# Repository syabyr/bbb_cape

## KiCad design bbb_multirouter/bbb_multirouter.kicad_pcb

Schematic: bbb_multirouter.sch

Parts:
J1: Conn_01x06; PinSocket_1x06_P2.54mm_Vertical
J2: Conn_01x02; PinSocket_1x02_P2.54mm_Vertical
J3: USB_C_Receptacle; USB_C_Receptacle_HRO_TYPE-C-31-M-12
P8, P9: BeagleBone_Black_Header; Socket_BeagleBone_Black
SW1, SW2, SW3: SW_Push; turtlekey

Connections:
+3V3: P9.3, P9.4; also elsewhere on the board
+5V: J3.A4 (VBUS), J3.A9 (VBUS), J3.B4 (VBUS), J3.B9 (VBUS), P9.5, P9.6
AIN0: P9.39
AIN1: P9.40
AIN2: P9.37
AIN3: P9.38
AIN4: P9.33
AIN5: P9.36
AIN6: P9.35
ECAPPWM0: P9.42
EHRPWM1A: P9.14
EHRPWM1B: P9.16
EHRPWM2A: P8.19
EHRPWM2B: P8.13
GND: J1.1, J3.A1 (GND), J3.A12 (GND), J3.B1 (GND), J3.B12 (GND), J3.S1 (SHIELD), P8.1, P8.2, P9.1, P9.2, P9.43, P9.44, P9.45, P9.46, SW1.2, SW2.2, SW3.2; also elsewhere on the board
GNDA_ADC: P9.34
GPIO_20: P9.41
GPIO_26: P8.14
GPIO_27: P8.17
GPIO_44: P8.12
GPIO_45: P8.11
GPIO_46: P8.16
GPIO_47: P8.15
GPIO_48: P9.15
GPIO_49: P9.23
GPIO_60: P9.12
GPIO_61: P8.26
GPIO_65: P8.18
GPIO_66: P8.7
GPIO_67: P8.8
GPIO_68: P8.10
GPIO_69: P8.9
GPIO_112: P9.30
GPIO_115: P9.27
GPIO_117: P9.25
I2C2_SCL: P9.19
I2C2_SDA: P9.20
LCD_AC_BIAS: P8.30
LCD_DATA0: P8.45; also elsewhere on the board
LCD_DATA1: P8.46; also elsewhere on the board
LCD_DATA2: P8.43, SW3.1
LCD_DATA3: P8.44
LCD_DATA4: P8.41
LCD_DATA5: P8.42
LCD_DATA6: P8.39
LCD_DATA7: P8.40
LCD_DATA8: P8.37
LCD_DATA9: P8.38
LCD_DATA10: P8.36
LCD_DATA11: P8.34
LCD_DATA12: P8.35
LCD_DATA13: P8.33
LCD_DATA14: P8.31
LCD_DATA15: P8.32
LCD_HSYNC: P8.29
LCD_PCLK: P8.28
LCD_VSYNC: P8.27
MMC1_CLK: P8.21
MMC1_CMD: P8.20
MMC1_DAT0: P8.25
MMC1_DAT1: P8.24
MMC1_DAT2: P8.5
MMC1_DAT3: P8.6
MMC1_DAT4: P8.23
MMC1_DAT5: P8.22
MMC1_DAT6: P8.3
MMC1_DAT7: P8.4
PWR_BUT: P9.9, SW1.1
SPI0_CS0: P9.17
SPI0_D0: P9.21
SPI0_D1: P9.18
SPI0_SCLK: P9.22
SPI1_CS0: P9.28
SPI1_D0: P9.29
SPI1_SCLK: P9.31
SYS_5V: P9.7, P9.8
SYS_RESETN: P9.10, SW2.1
UART0_RX: J1.4; also elsewhere on the board
UART0_TX: J1.5; also elsewhere on the board
UART1_RXD: P9.26; also elsewhere on the board
UART1_TXD: P9.24; also elsewhere on the board
UART4_RXD: P9.11
UART4_TXD: P9.13
USB_DM: J2.1; also elsewhere on the board
USB_DP: J2.2; also elsewhere on the board
VDD_ADC: P9.32

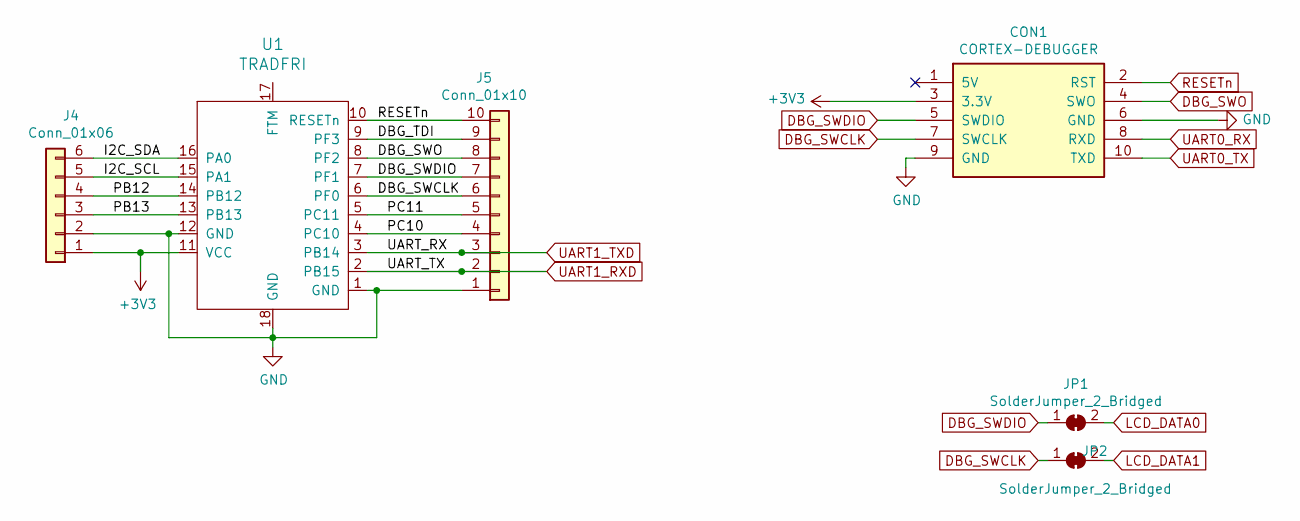
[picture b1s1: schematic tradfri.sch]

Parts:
CON1: CORTEX-DEBUGGER; debugger_2x05_P1.27mm_Vertical
J4: Conn_01x06; PinHeader_1x06_P2.54mm_Vertical
J5: Conn_01x10; PinHeader_1x10_P2.54mm_Vertical
JP1, JP2: SolderJumper_2_Bridged; SolderJumper-2_P1.3mm_Open_Pad1.0x1.5mm
U1: TRADFRI

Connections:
+3V3: CON1.3 (3.3V), J4.1, U1.11 (VCC); also elsewhere on the board
/Sheet5FB19A08/DBG_TDI: J5.9, U1.9 (PF3)
/Sheet5FB19A08/I2C_SCL: J4.5, U1.15 (PA1)
/Sheet5FB19A08/I2C_SDA: J4.6, U1.16 (PA0)
/Sheet5FB19A08/PB12: J4.4, U1.14 (PB12)
/Sheet5FB19A08/PB13: J4.3, U1.13 (PB13)
/Sheet5FB19A08/PC10: J5.4, U1.4 (PC10)
/Sheet5FB19A08/PC11: J5.5, U1.5 (PC11)
DBG_SWCLK: CON1.7 (SWCLK), J5.6, JP2.1 (A), U1.6 (PF0)
DBG_SWDIO: CON1.5 (SWDIO), J5.7, JP1.1 (A), U1.7 (PF1)
DBG_SWO: CON1.4 (SWO), J5.8, U1.8 (PF2)
GND: CON1.6 (GND), CON1.9 (GND), J4.2, J5.1, U1.1 (GND), U1.12 (GND), U1.18 (GND); also elsewhere on the board
LCD_DATA0: JP1.2 (B); also elsewhere on the board
LCD_DATA1: JP2.2 (B); also elsewhere on the board
RESETn: CON1.2 (RST), J5.10, U1.10 (RESETn)
UART0_RX: CON1.8 (RXD); also elsewhere on the board
UART0_TX: CON1.10 (TXD); also elsewhere on the board
UART1_RXD: J5.2, U1.2 (PB15); also elsewhere on the board
UART1_TXD: J5.3, U1.3 (PB14); also elsewhere on the board

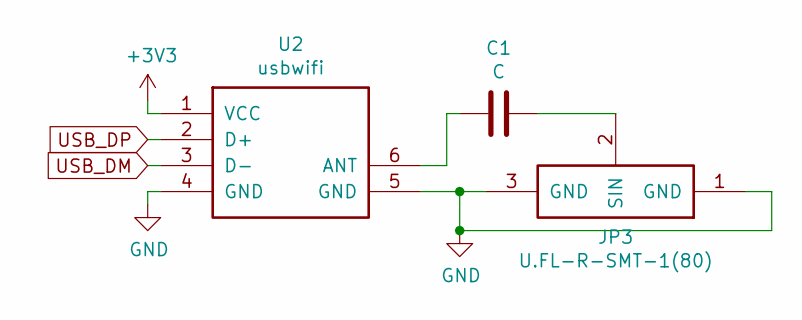
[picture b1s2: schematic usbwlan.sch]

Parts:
C1: C; C_0603_1608Metric_Pad1.08x0.95mm_HandSolder
JP3: U.FL-R-SMT-1(80); RF-SMD_U.FL-R-SMT-1(80)
U2: usbwifi; RTL8188CUS

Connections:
+3V3: U2.1 (VCC); also elsewhere on the board
GND: JP3.1 (GND), JP3.3 (GND), U2.4 (GND), U2.5 (GND); also elsewhere on the board
unnamed: C1.1, JP3.2 (SIN)
unnamed: C1.2, U2.6 (ANT)
USB_DM: U2.3 (D-); also elsewhere on the board
USB_DP: U2.2 (D+); also elsewhere on the board

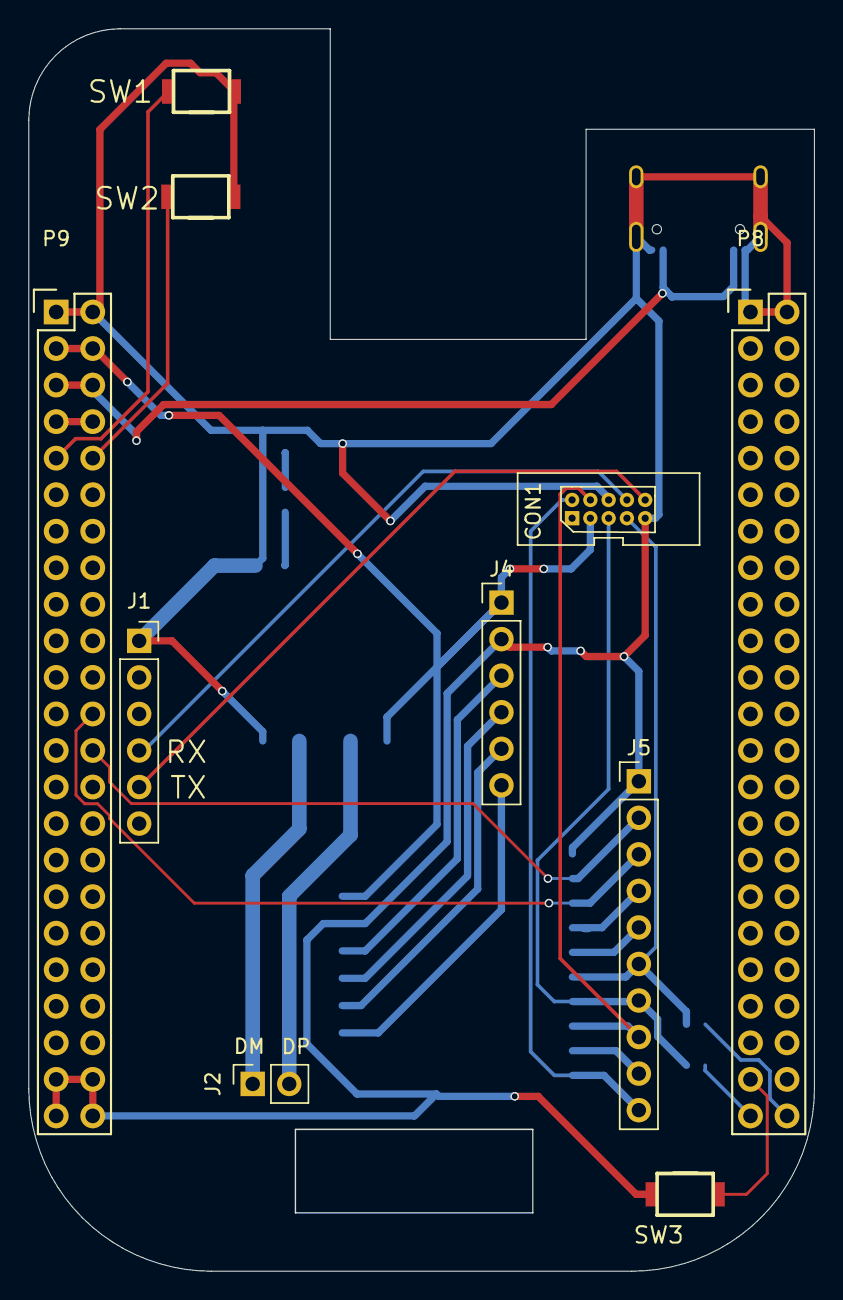
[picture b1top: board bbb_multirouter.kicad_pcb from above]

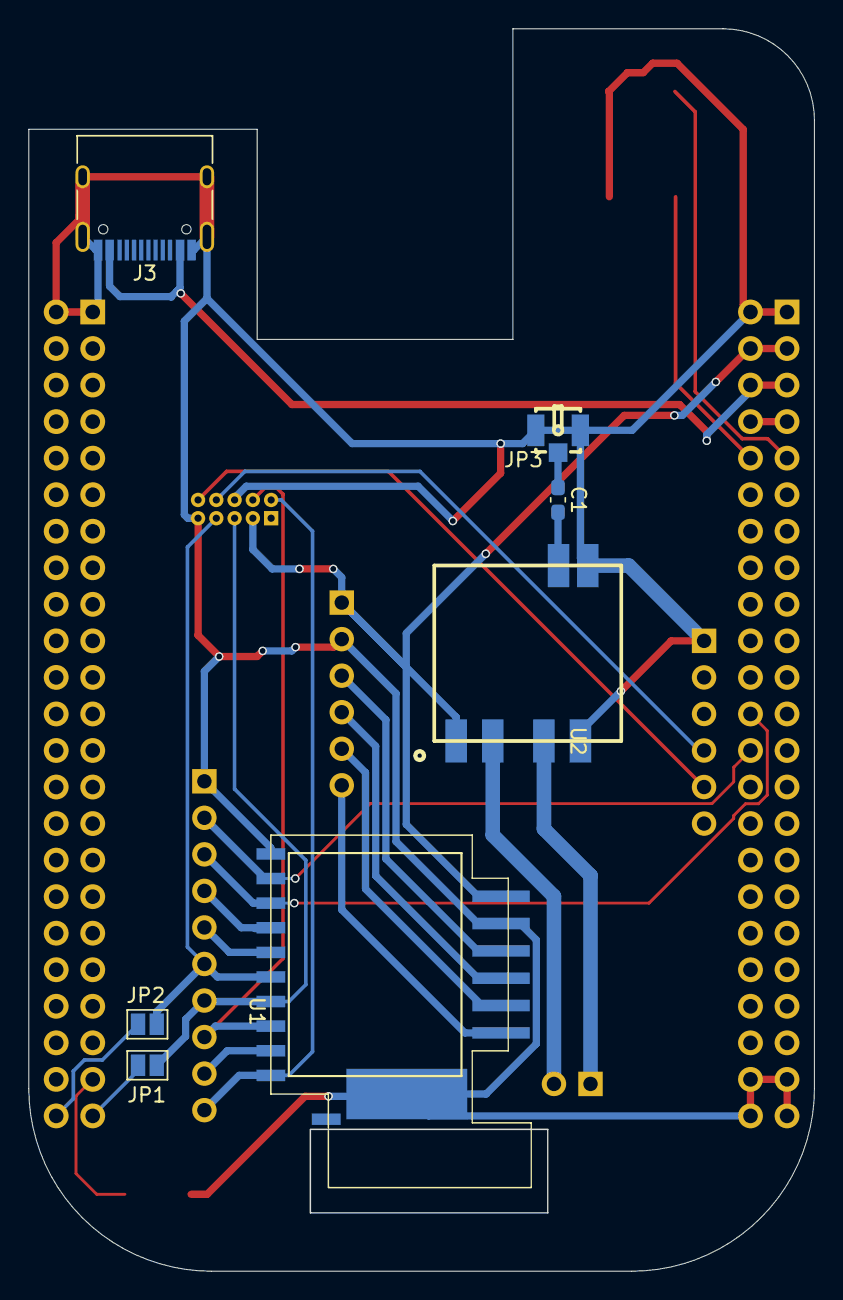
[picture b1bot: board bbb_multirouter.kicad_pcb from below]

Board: 2 copper layers, 54.5 x 86.3 mm, 17 parts (7 on the bottom side), 28 nets.

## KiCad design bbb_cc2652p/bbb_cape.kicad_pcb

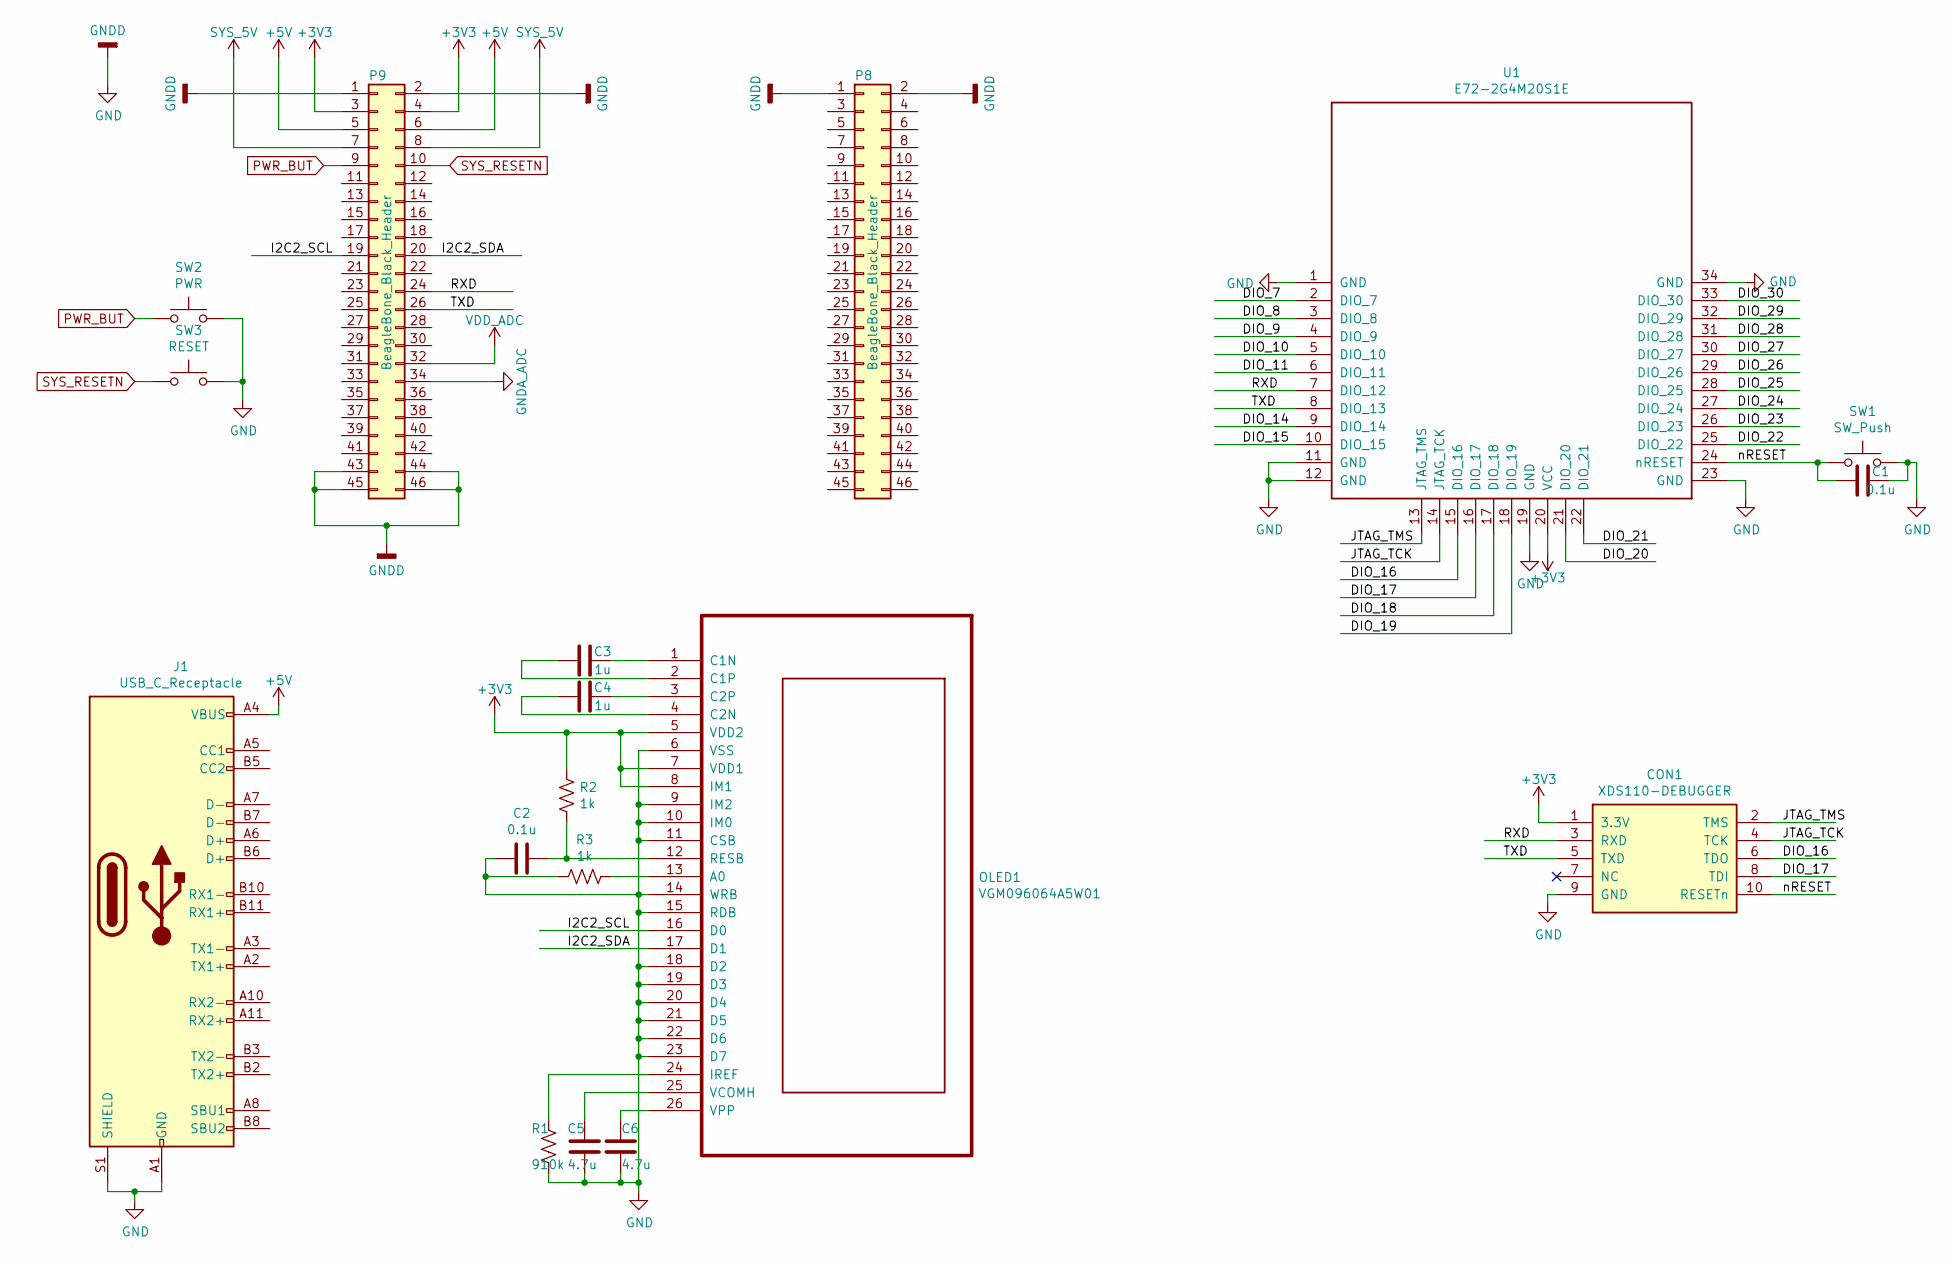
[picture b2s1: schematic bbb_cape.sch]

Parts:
C1, C2: 0.1u; C_0603_1608Metric_Pad1.08x0.95mm_HandSolder
C3, C4: 1u; C_0805_2012Metric_Pad1.18x1.45mm_HandSolder
C5, C6: 4.7u; C_0805_2012Metric_Pad1.18x1.45mm_HandSolder
CON1: XDS110-DEBUGGER; debugger_2x05_P1.27mm_Vertical
J1: USB_C_Receptacle; USB_C_Receptacle_HRO_TYPE-C-31-M-12
OLED1: VGM096064A5W01
P8, P9: BeagleBone_Black_Header; Socket_BeagleBone_Black
R1: 910k; R_0603_1608Metric_Pad0.98x0.95mm_HandSolder
R2, R3: 1k; R_0603_1608Metric_Pad0.98x0.95mm_HandSolder
SW1: SW_Push; turtlekey
SW2: PWR; turtlekey
SW3: RESET; turtlekey
U1: E72-2G4M20S1E

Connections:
+3V3: CON1.1 (3.3V), OLED1.5 (VDD2), OLED1.7 (VDD1), OLED1.8 (IM1), P9.3, P9.4, R2.1, U1.20 (VCC)
+5V: J1.A4 (VBUS), J1.A9 (VBUS), J1.B4 (VBUS), J1.B9 (VBUS), P9.5, P9.6
/DIO_7: U1.2 (DIO_7)
/DIO_8: U1.3 (DIO_8)
/DIO_9: U1.4 (DIO_9)
/DIO_10: U1.5 (DIO_10)
/DIO_11: U1.6 (DIO_11)
/DIO_14: U1.9 (DIO_14)
/DIO_15: U1.10 (DIO_15)
/DIO_16: CON1.6 (TDO), U1.15 (DIO_16)
/DIO_17: CON1.8 (TDI), U1.16 (DIO_17)
/DIO_18: U1.17 (DIO_18)
/DIO_19: U1.18 (DIO_19)
/DIO_20: U1.21 (DIO_20)
/DIO_21: U1.22 (DIO_21)
/DIO_22: U1.25 (DIO_22)
/DIO_23: U1.26 (DIO_23)
/DIO_24: U1.27 (DIO_24)
/DIO_25: U1.28 (DIO_25)
/DIO_26: U1.29 (DIO_26)
/DIO_27: U1.30 (DIO_27)
/DIO_28: U1.31 (DIO_28)
/DIO_29: U1.32 (DIO_29)
/DIO_30: U1.33 (DIO_30)
/I2C2_SCL: OLED1.16 (D0), P9.19
/I2C2_SDA: OLED1.17 (D1), P9.20
/JTAG_TCK: CON1.4 (TCK), U1.14 (JTAG_TCK)
/JTAG_TMS: CON1.2 (TMS), U1.13 (JTAG_TMS)
/RXD: CON1.3 (RXD), P9.24, U1.7 (DIO_12)
/TXD: CON1.5 (TXD), P9.26, U1.8 (DIO_13)
/nRESET: C1.2, CON1.10 (RESETn), SW1.1, U1.24 (nRESET)
GND: C1.1, C2.2, C5.1, C6.1, CON1.9 (GND), J1.A1 (GND), J1.A12 (GND), J1.B1 (GND), J1.B12 (GND), J1.S1 (SHIELD), OLED1.6 (VSS), OLED1.9 (IM2), OLED1.10 (IM0), OLED1.11 (CSB), OLED1.14 (WRB), OLED1.15 (RDB), OLED1.18 (D2), OLED1.19 (D3), OLED1.20 (D4), OLED1.21 (D5), OLED1.22 (D6), OLED1.23 (D7), P8.1, P8.2, P9.1, P9.2, P9.43, P9.44, P9.45, P9.46, R1.1, R3.2, SW1.2, SW2.2, SW3.2, U1.1 (GND), U1.11 (GND), U1.12 (GND), U1.19 (GND), U1.23 (GND), U1.34 (GND)
GNDA_ADC: P9.34
unnamed: C2.1, OLED1.12 (RESB), R2.2
unnamed: C3.1, OLED1.1 (C1N)
unnamed: C3.2, OLED1.2 (C1P)
unnamed: C4.1, OLED1.3 (C2P)
unnamed: C4.2, OLED1.4 (C2N)
unnamed: C5.2, OLED1.25 (VCOMH)
unnamed: C6.2, OLED1.26 (VPP)
unnamed: OLED1.13 (A0), R3.1
unnamed: OLED1.24 (IREF), R1.2
PWR_BUT: P9.9, SW2.1
SYS_5V: P9.7, P9.8
SYS_RESETN: P9.10, SW3.1
VDD_ADC: P9.32

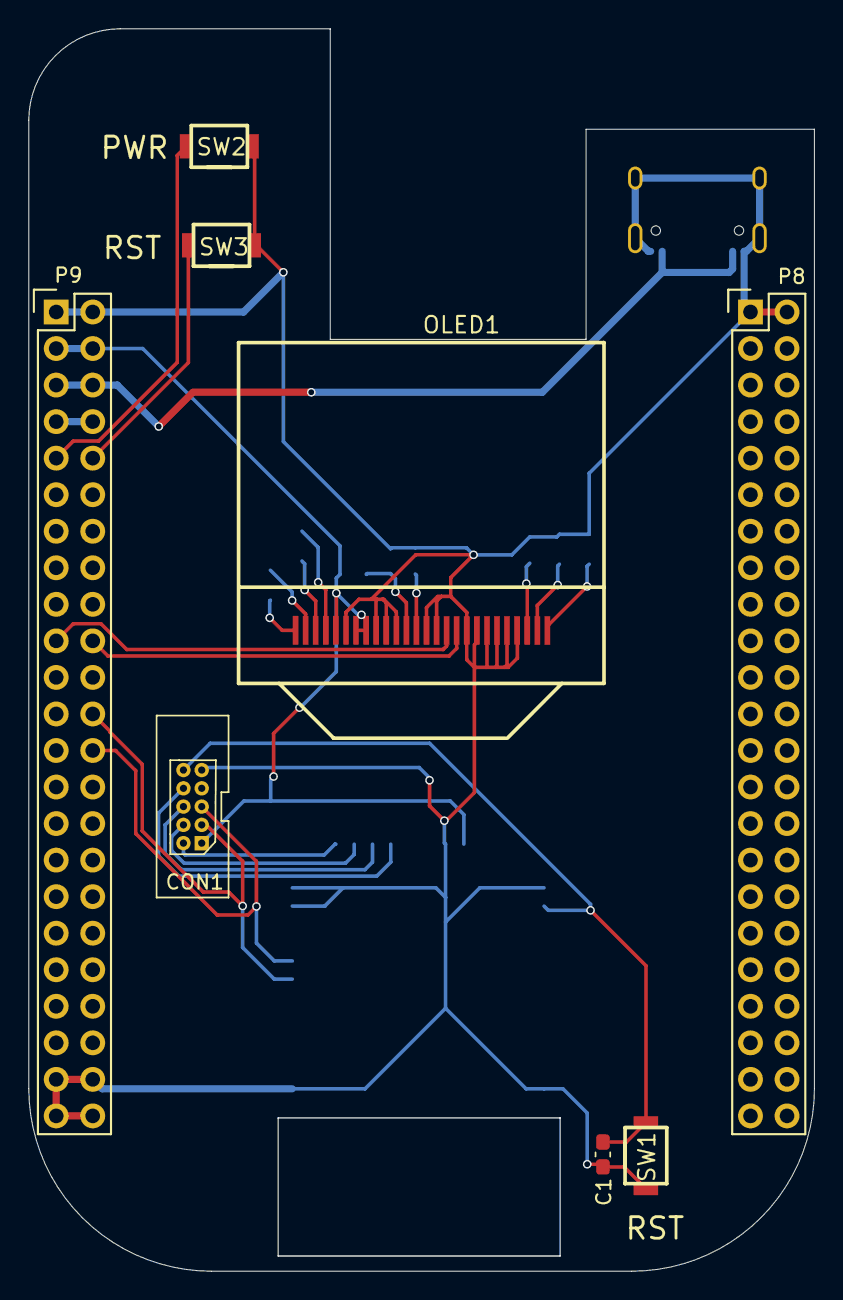
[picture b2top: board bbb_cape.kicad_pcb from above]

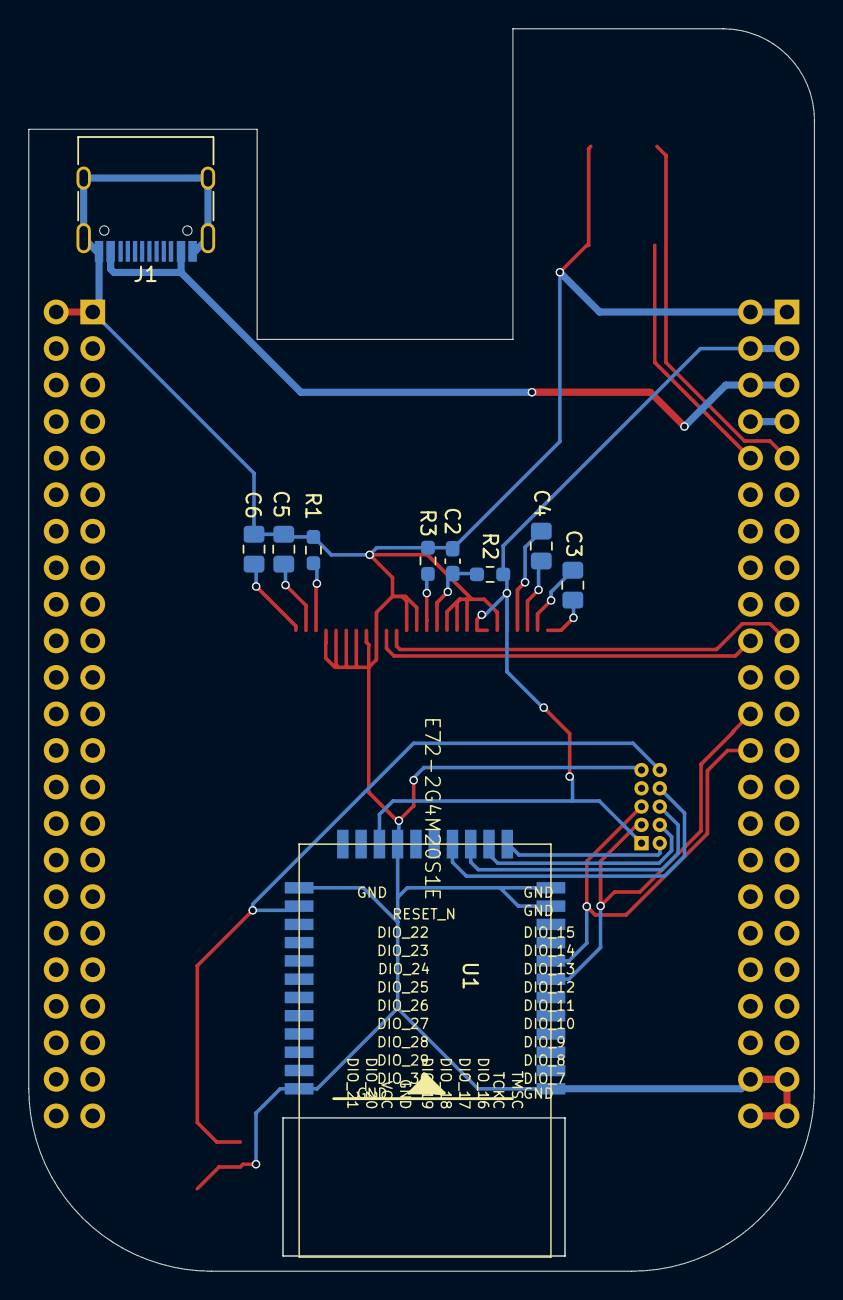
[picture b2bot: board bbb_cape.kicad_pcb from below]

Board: 2 copper layers, 54.5 x 86.3 mm, 18 parts (11 on the bottom side), 24 nets.

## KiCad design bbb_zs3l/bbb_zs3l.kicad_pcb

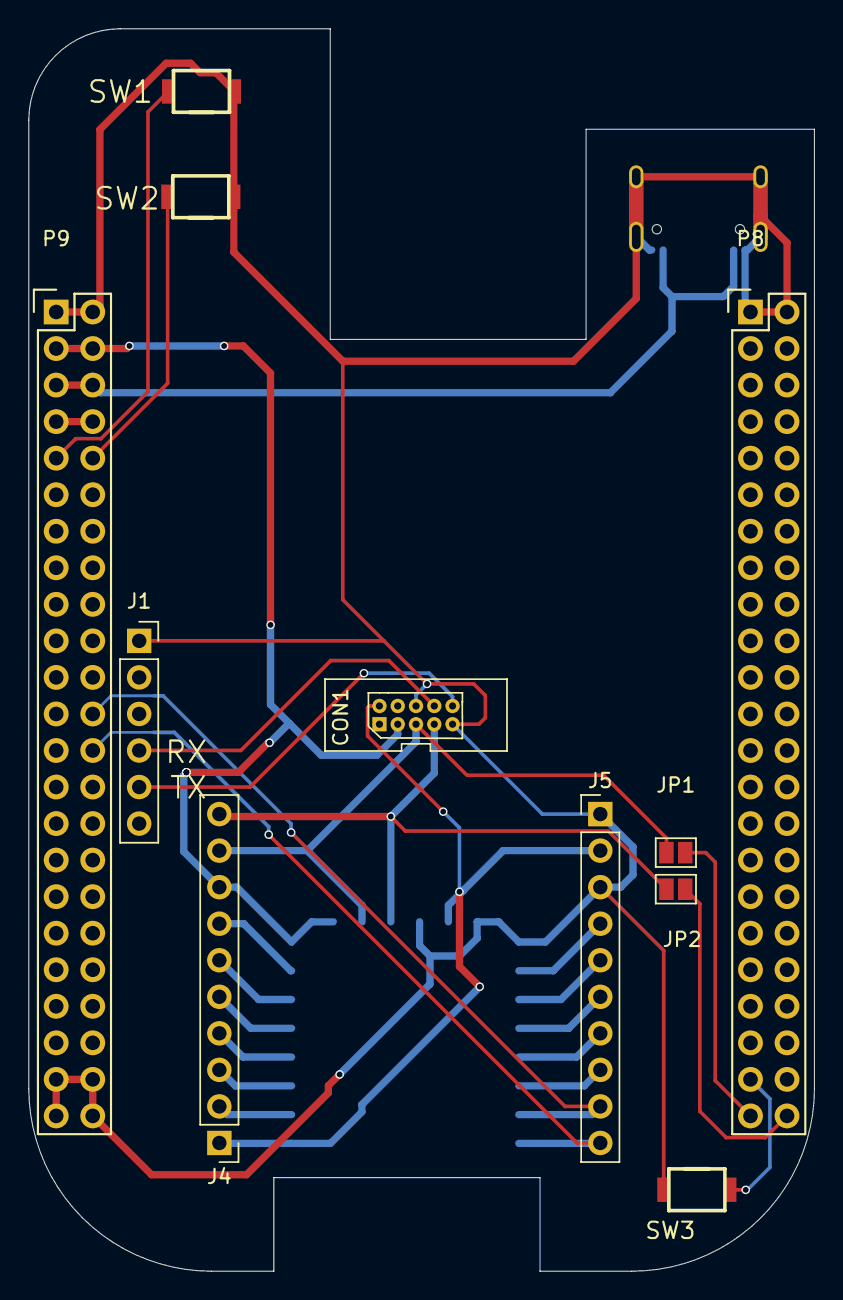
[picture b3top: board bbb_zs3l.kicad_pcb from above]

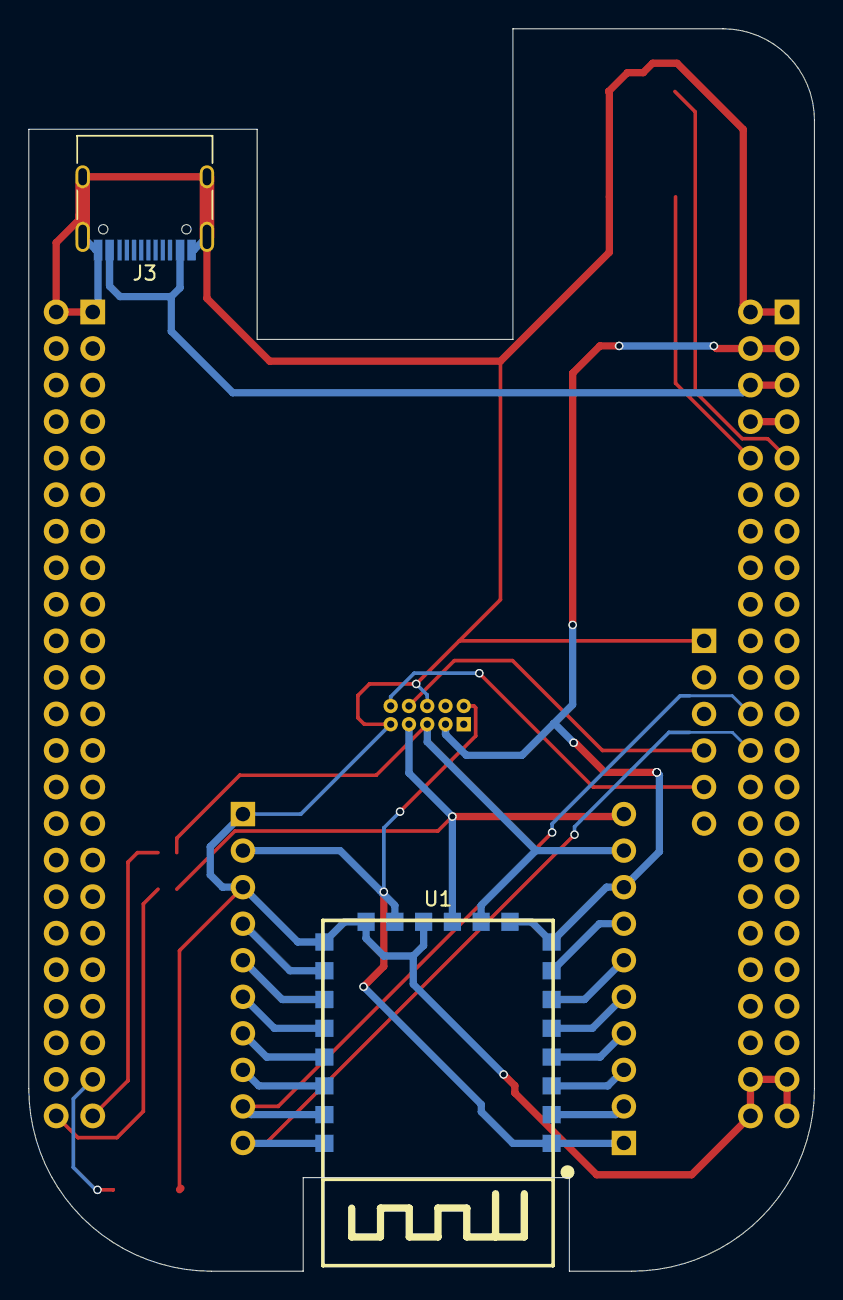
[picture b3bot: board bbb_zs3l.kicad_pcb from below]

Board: 2 copper layers, 54.6 x 86.4 mm, 13 parts (2 on the bottom side), 27 nets.

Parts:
CON1: CORTEX-DEBUGGER; debugger_2x05_P1.27mm_Vertical
J1: Conn_01x06; PinSocket_1x06_P2.54mm_Vertical
J3: USB_C_Receptacle; USB_C_Receptacle_HRO_TYPE-C-31-M-12
J4, J5: Conn_01x10; PinHeader_1x10_P2.54mm_Vertical
JP1, JP2: SolderJumper_2_Bridged; SolderJumper-2_P1.3mm_Open_Pad1.0x1.5mm
P8, P9: BeagleBone_Black_Header; Socket_BeagleBone_Black
SW1, SW2, SW3: SW_Push; turtlekey
U1: ZS3L

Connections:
+3V3: CON1.3, J4.8, P9.3, P9.4, U1.8, U1.17
+5V: J3.A4, J3.A9, J3.B4, J3.B9, P9.5, P9.6
/Sheet5FB5E9C3/ADC_PC01: J4.2, U1.2
/Sheet5FB5E9C3/PA00: J4.5, U1.5
/Sheet5FB5E9C3/PA03: J4.6, U1.6
/Sheet5FB5E9C3/PA04: J4.7, U1.7
/Sheet5FB5E9C3/PB00: J5.7, U1.13
/Sheet5FB5E9C3/PB01: J5.8, U1.14
/Sheet5FB5E9C3/PC00: J4.4, U1.4
/Sheet5FB5E9C3/PC02: J5.6, U1.12
/Sheet5FB5E9C3/PD00: J5.5, U1.11
/Sheet5FB5E9C3/PD01: J5.4, U1.10
DBG_SWCLK: CON1.7, J4.10, JP2.1, U1.19
DBG_SWDIO: CON1.5, J4.9, JP1.1, U1.18
GND: CON1.6, CON1.9, J1.1, J3.A1, J3.A12, J3.B1, J3.B12, J3.S1, J5.1, J5.3, P8.1, P8.2, P9.1, P9.2, P9.43, P9.44, P9.45, P9.46, SW1.2, SW2.2, SW3.2, U1.9, U1.20, U1.22
LCD_DATA0: JP1.2, P8.45
LCD_DATA1: JP2.2, P8.46
LCD_DATA2: P8.43, SW3.1
unnamed: J4.3, U1.3
PWR_BUT: P9.9, SW1.1
RESETn: CON1.2, J4.1, J5.2, U1.1, U1.21
SYS_5V: P9.7, P9.8
SYS_RESETN: P9.10, SW2.1
UART0_RX: CON1.8, J1.4
UART0_TX: CON1.10, J1.5
UART1_RXD: J5.10, P9.26, U1.16
UART1_TXD: J5.9, P9.24, U1.15

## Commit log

2021-02-16 bbb_zs3l
2021-02-17 cc2652 wifi
2021-02-17 usb wifi
